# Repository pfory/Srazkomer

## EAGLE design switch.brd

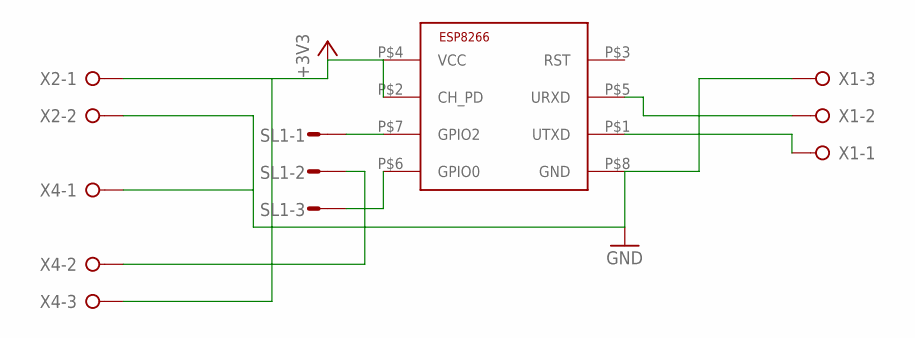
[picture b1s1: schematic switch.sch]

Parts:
SL1: M03S; 03P
U$1: ESP8266-01; ESP-01
X1, X4: W237-3E
X2: W237-02P; W237-132

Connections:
+3V3: U$1.P$2 (CH_PD), U$1.P$4 (VCC), X2.1, X4.3
GND: U$1.P$8 (GND), X1.3, X2.2, X4.1
GPIO0: SL1.3, U$1.P$6 (GPIO0)
GPIO2: SL1.1, U$1.P$7 (GPIO2)
unnamed: U$1.P$5 (URXD), X1.2
unnamed: SL1.2, X4.2
unnamed: U$1.P$1 (UTXD), X1.1

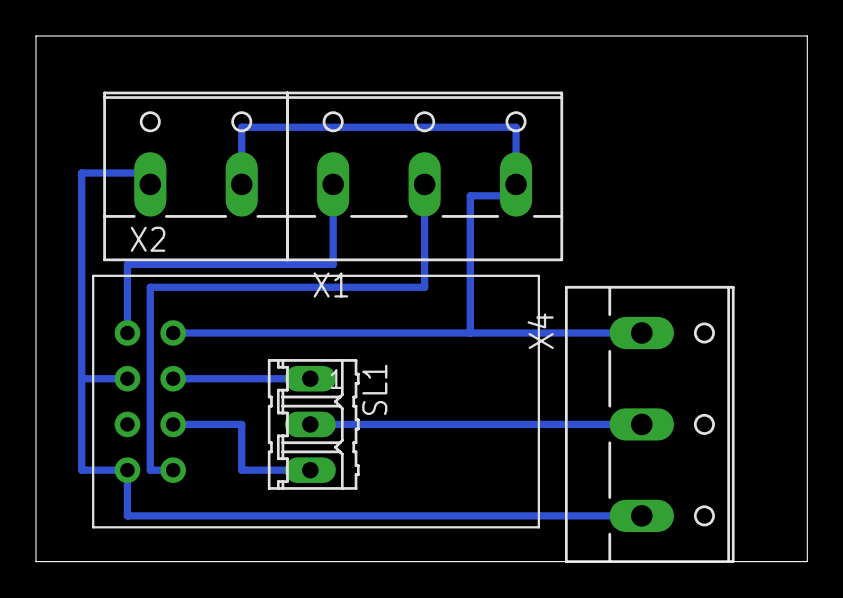
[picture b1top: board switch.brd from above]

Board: 2 copper layers, 42.9 x 29.2 mm, 5 parts (0 on the bottom side), 7 nets.

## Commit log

2016-04-05 initial version 0.1
2016-04-20 +autoconnect
2016-05-04 +upravy kodu
2016-05-04 +config
2016-05-20 +v03 restart z GUI
2016-05-25 v0.4 + reconnect each 10 minutes
2016-05-25 +gitignore
2016-06-01 +zasilani verze v HB
2016-07-04 v0,5 lua 151 4.7.2016
2016-07-26 pi na chate
2017-01-09 funkcni verze
2017-01-10 +bootreason
2017-01-14 verze 0,61 arduino
2017-02-27 oprava mereni delky pulsu
2017-08-29 verze s hall snimacem
2017-08-29 archivace lua verze
2017-09-12 verze
2018-01-11 zmena poctu pulsu v konfigu
2018-05-24 zmena pocitani impulsu, nove se posila jen pocet impulsu za posledni interval (1 minuta) a HB + verze.
2018-05-24 odstraneni nadbytecnych funkci
2018-05-24 interval na 10 minut
2018-05-24 verze 0,8
2018-05-25 zmena posilani impulsu
2018-05-28 handle
2018-06-11 - pevna IP - pojmenovani AP
2018-06-11 0.82
2018-06-13 hb ted udava pocet minut od posledniho restartu prvni odeslany hb by mel byt status posledniho resetu, pak uz se po kazde minute pricte 1
2018-06-14 skript pro OTA update
2018-06-22 v0.84 - opravena chyba, nevynulovani promenne pro ukladani poctu pulzu kdyz byla vetsi nez 60, zakmity
2018-07-10 kosmeticke upravy kodu
2018-07-10 verze 0.85 - pulz se zapocita jen jednou za 5s
2018-07-11 0.86 -zmena spousteci hrany
2018-08-20 zmena autoconnectu
2018-08-23 portspeed
2018-08-27 timeout v0,9
2018-10-07 v 0.91 led
2018-11-01 v1.0 - upravy pro neblokujici wifimanager mqtt odesilani pres sender
2018-11-20 v1.0
2019-03-07 json 6
2019-03-08 -sender
2019-08-06 1.21
2019-09-30 oprava resetu pres MQTT
2020-07-23 + configuration.h a prislusne upravy kodu
2021-07-06 kosmetika
2021-07-08 interval mezi pulsy zmenšen na 1s
2021-12-02 v1.6
2021-12-07 1.70
2021-12-12 1.71
2022-09-16 cisteni kodu
2024-08-27 převedeno na Tasmota
2025-08-20 nový hw
